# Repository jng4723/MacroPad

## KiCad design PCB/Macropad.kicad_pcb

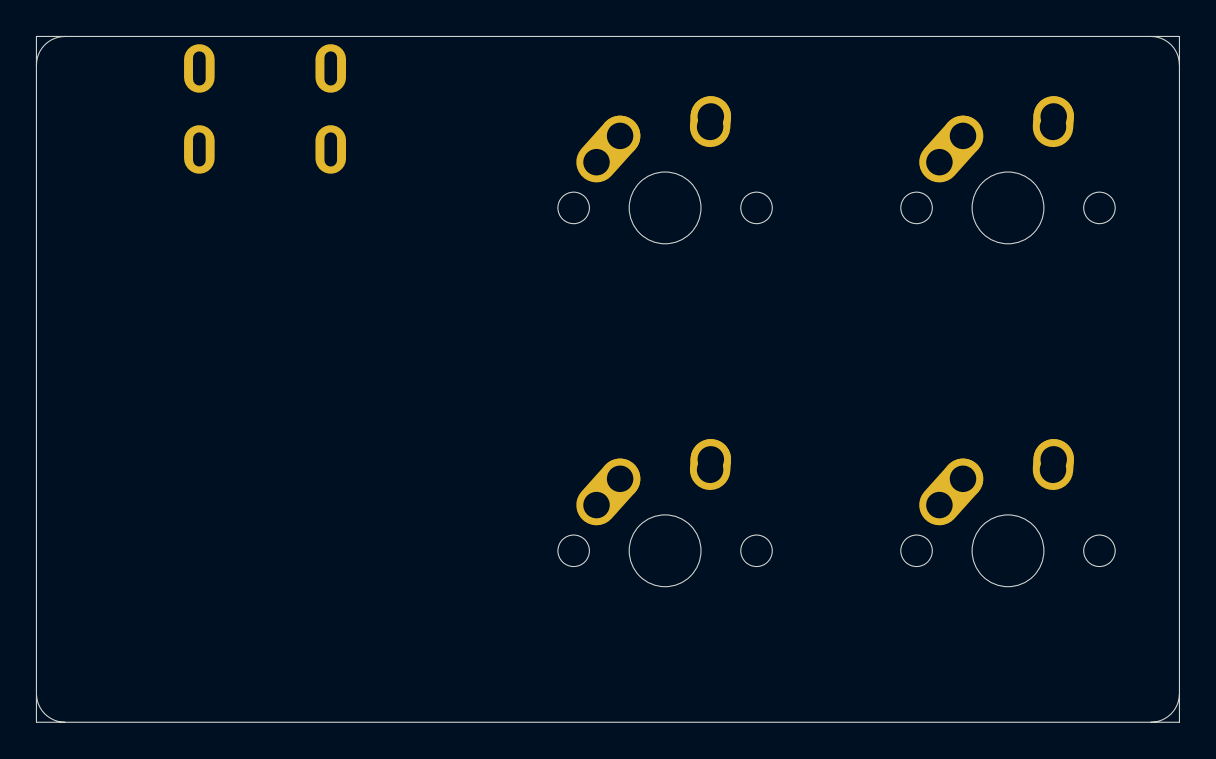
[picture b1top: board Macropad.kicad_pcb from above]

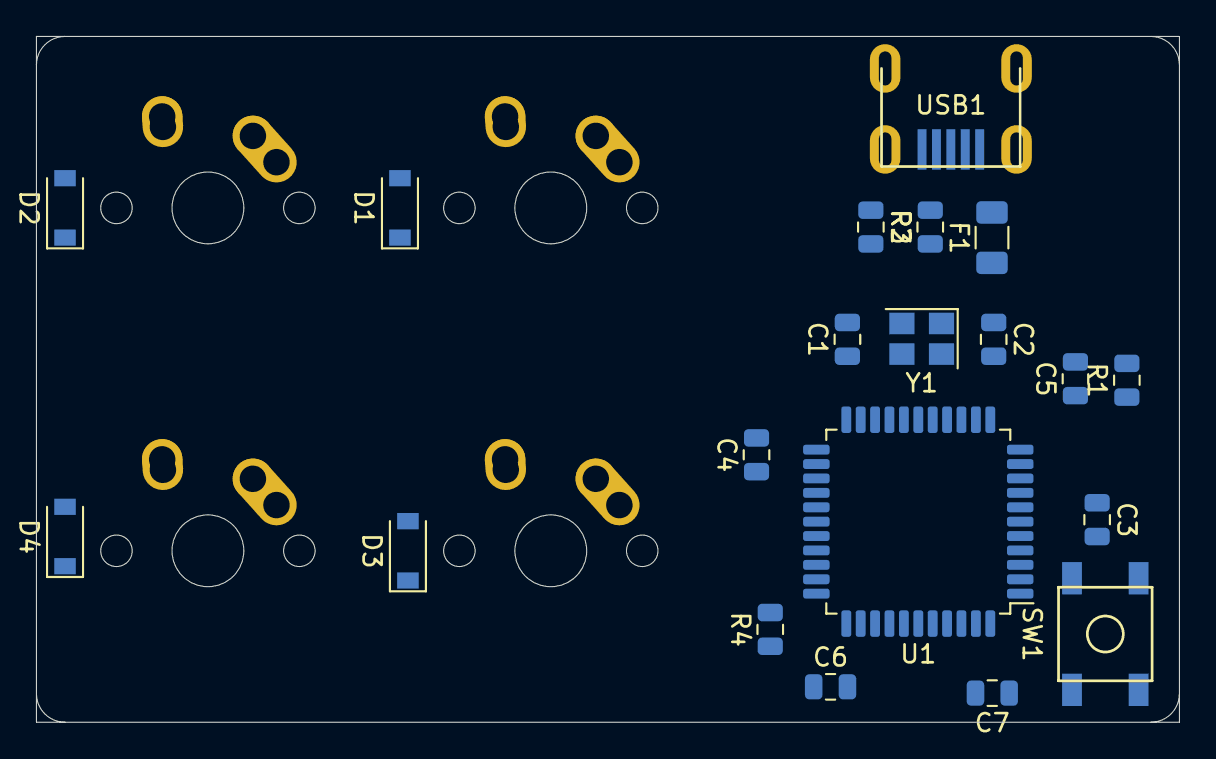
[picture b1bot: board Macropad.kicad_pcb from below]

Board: 2 copper layers, 63.5 x 38.1 mm, 24 parts (20 on the bottom side), 20 nets, no tracks yet.

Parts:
C1, C2: 22pF; C_0805_2012Metric
C3: 1uf; C_0805_2012Metric
C4, C5, C6: 0.1uf; C_0805_2012Metric
C7: 10uf; C_0805_2012Metric
D1, D2, D3, D4: D_Small; D_SOD-123
F1: Polyfuse; Fuse_1206_3216Metric
MX1, MX2, MX3, MX4: MX-NoLED; MX-1U-NoLED
R1: 10k; R_0805_2012Metric
R2, R3: 22; R_0805_2012Metric
R4: 10K; R_0805_2012Metric
SW1: SW_Push; SKQG-1155865
U1: ATmega32U4-AU; LQFP-44_10x10mm_P0.8mm
USB1: Molex-0548190589
Y1: 16MHz; Crystal_SMD_3225-4Pin_3.2x2.5mm

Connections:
+5V: C4.1, C5.1, C6.1, C7.1, F1.1, R1.1, U1.2, U1.7, U1.14, U1.24, U1.34, U1.44
COL0: MX1.1, MX3.1
COL1: MX2.1, MX4.1
D+: R2.2, USB1.3
D-: R3.2, USB1.4
GND: C1.1, C2.1, C3.2, C4.2, C5.2, C6.2, C7.2, R4.1, SW1.1, U1.5, U1.15, U1.23, U1.35, U1.43, USB1.1, Y1.2, Y1.4
unnamed: C1.2, U1.17, Y1.1
unnamed: C2.2, U1.16, Y1.3
unnamed: C3.1, U1.6
unnamed: D1.2, MX1.2
unnamed: D2.2, MX2.2
unnamed: D3.2, MX3.2
unnamed: D4.2, MX4.2
unnamed: R1.2, SW1.2, U1.13
unnamed: R2.1, U1.4
unnamed: R3.1, U1.3
unnamed: R4.2, U1.33
ROW0: D1.1, D2.1
ROW1: D3.1, D4.1
VCC: F1.2, USB1.5

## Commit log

2020-11-20 Create PCB
    PCB design files
2020-11-20 PCB Deisgn Files
2020-11-21 Added MCU
2021-01-06 Footprints added
2021-01-07 Components Placed, Routing to be done
